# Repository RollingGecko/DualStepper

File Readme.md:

#DualStepper

The DualStepper is an adapter board to work with two stepper drivers in parallel sharing one step and direction signal and to drive 2 stepper motors.
It should be compatible with the following steppers

* SilentStepStick https://github.com/watterott/SilentStepStick
* StepStick http://reprap.org/wiki/StepStick
* A4988 https://www.pololu.com/product/1182

Additionaly there is also a conector board designed, to bring GND, +5V, step, DIR out from the main board's stepper socket.

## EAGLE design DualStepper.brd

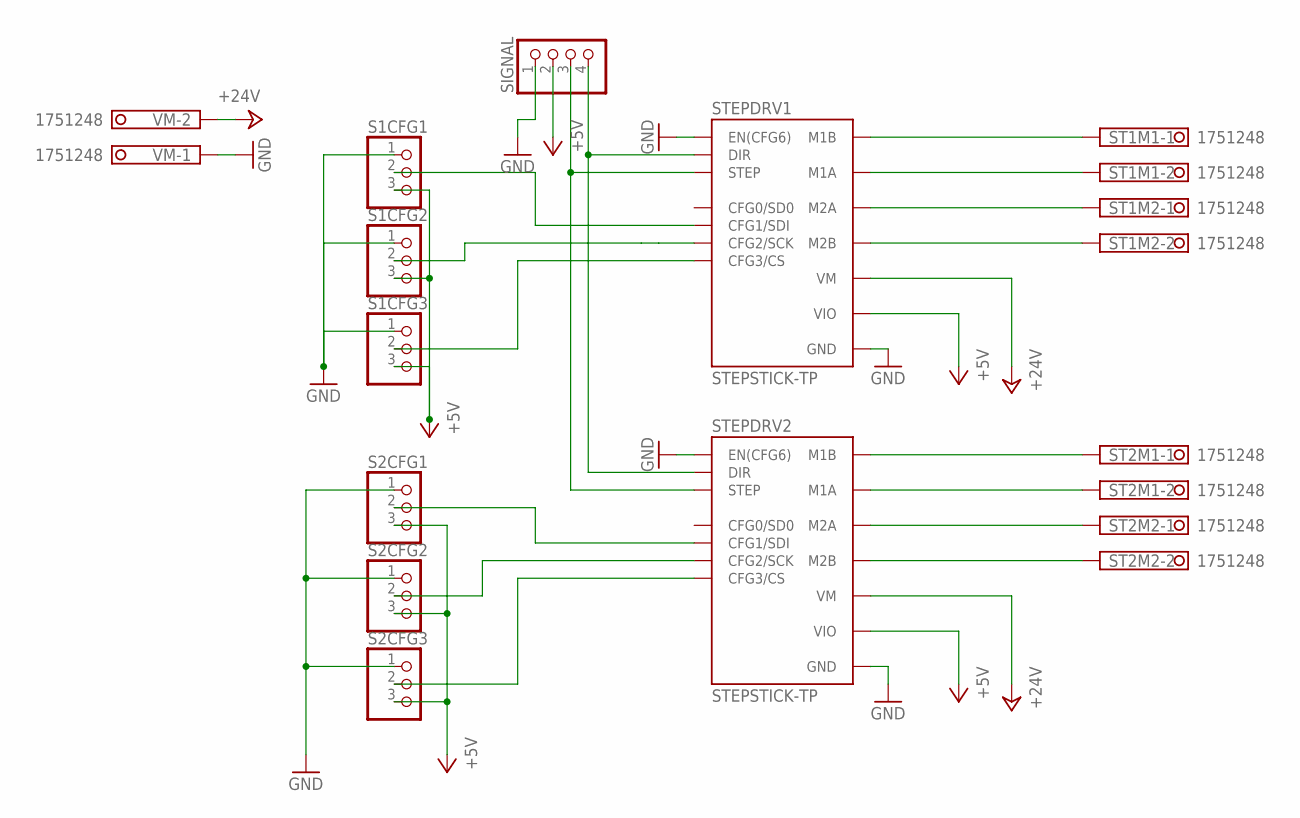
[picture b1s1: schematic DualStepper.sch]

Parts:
S1CFG1, S1CFG2, S1CFG3, S2CFG1, S2CFG2, S2CFG3: PINHD-1X3; 1X03
SIGNAL: PINHD-1X4; 1X04
ST1M1, ST1M2, ST2M1, ST2M2: 1751248
STEPDRV1, STEPDRV2: STEPSTICK-TP; STEPSTICK_TP
VM: 1751248

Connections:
+5V: S1CFG1.3, S1CFG2.3, S1CFG3.3, S2CFG1.3, S2CFG2.3, S2CFG3.3, SIGNAL.2, STEPDRV1.VIO, STEPDRV2.VIO
+24V: STEPDRV1.VM, STEPDRV2.VM, VM.2
GND: S1CFG1.1, S1CFG2.1, S1CFG3.1, S2CFG1.1, S2CFG2.1, S2CFG3.1, SIGNAL.1, STEPDRV1.EN (EN(CFG6)), STEPDRV1.GND@1 (GND), STEPDRV1.GND@2 (GND), STEPDRV2.EN (EN(CFG6)), STEPDRV2.GND@1 (GND), STEPDRV2.GND@2 (GND), VM.1
unnamed: ST1M2.2, STEPDRV1.M2B
unnamed: ST1M2.1, STEPDRV1.M2A
unnamed: ST1M1.2, STEPDRV1.M1A
unnamed: ST1M1.1, STEPDRV1.M1B
unnamed: ST2M1.1, STEPDRV2.M1B
unnamed: ST2M1.2, STEPDRV2.M1A
unnamed: ST2M2.1, STEPDRV2.M2A
unnamed: ST2M2.2, STEPDRV2.M2B
unnamed: S2CFG1.2, STEPDRV2.CFG1 (CFG1/SDI)
unnamed: S2CFG2.2, STEPDRV2.CFG2 (CFG2/SCK)
unnamed: S2CFG3.2, STEPDRV2.CFG3 (CFG3/CS)
unnamed: S1CFG2.2, STEPDRV1.CFG2 (CFG2/SCK)
unnamed: S1CFG3.2, STEPDRV1.CFG3 (CFG3/CS)
unnamed: S1CFG1.2, STEPDRV1.CFG1 (CFG1/SDI)
unnamed: SIGNAL.4, STEPDRV1.DIR, STEPDRV2.DIR
unnamed: SIGNAL.3, STEPDRV1.STEP, STEPDRV2.STEP

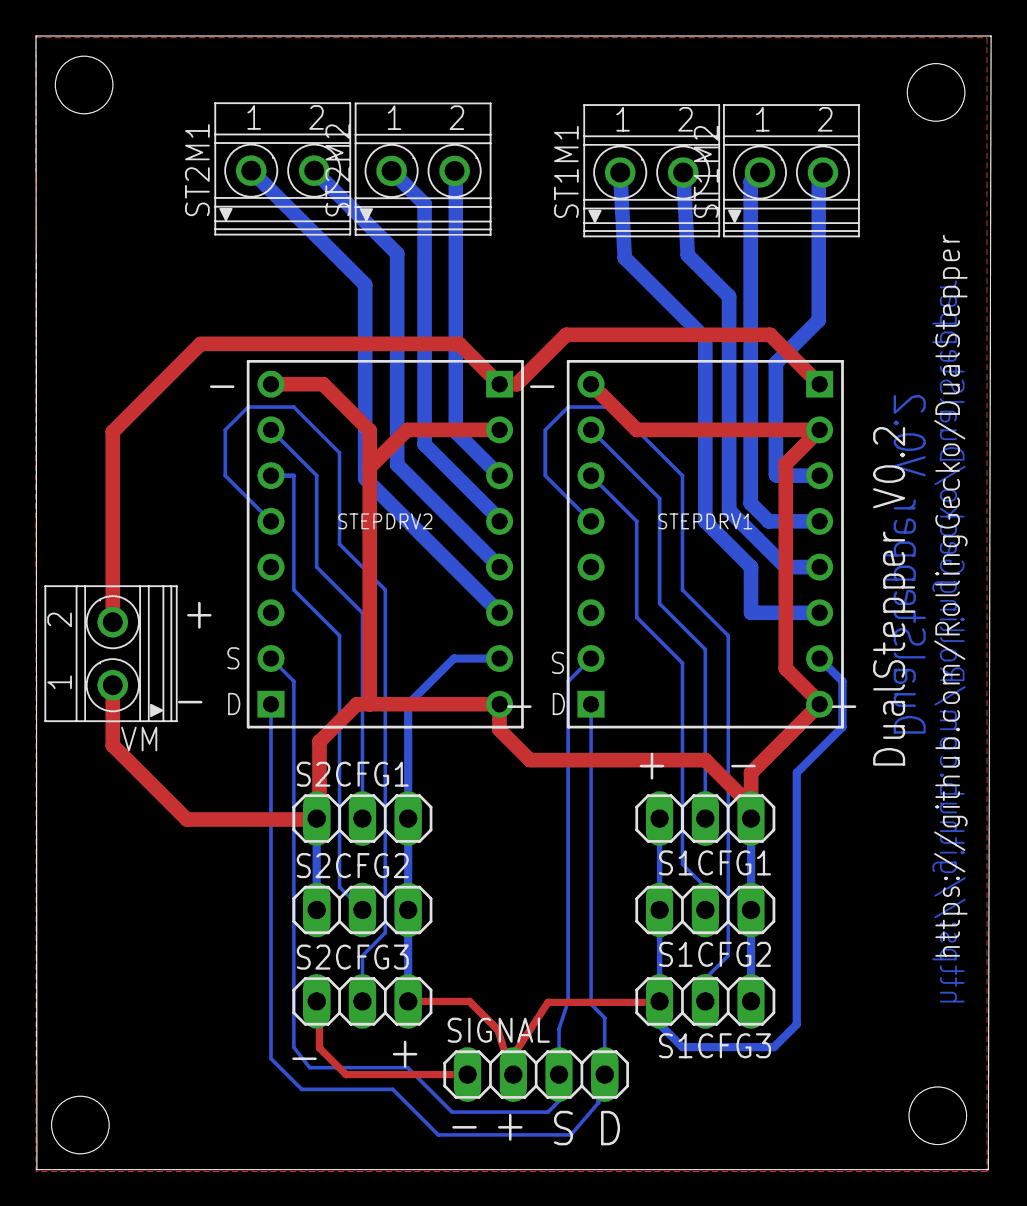
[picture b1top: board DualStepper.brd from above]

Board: 2 copper layers, 53.1 x 63.0 mm, 14 parts (0 on the bottom side), 19 nets.

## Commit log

2017-02-08 Initial
2017-02-08 Final design with Phoenix conector to stepper and V+24V
2017-02-09 Changed wire connectors to 5 mm grid
2017-02-09 Finael Version V0.1 for test
2017-02-09 Readme.md added
2017-02-09 CC BY-NC-ND 3.0 license added
2017-02-09 Formating changed
2017-02-09 Some correction to the readme.md file
2017-02-12 Eliminated one air wire
2017-02-12 Changed connectors to 3.5 RT
2017-02-12 Added WireConenctor.* as a PCB to bring out +5V, GND, STEP, DIR from stepper driver socket
2017-02-12 Holes corrected
2017-02-12 Added PartNaming
2017-02-12 one Pin Namign added
2017-02-12 Readme.md changed
2017-02-13 Minor changes
2017-02-13 Changed PWR connection position 2 Layer design GND Plate both sites Naming completed
2017-02-14 Some labels added
2017-02-21 Remark for aisler removed
